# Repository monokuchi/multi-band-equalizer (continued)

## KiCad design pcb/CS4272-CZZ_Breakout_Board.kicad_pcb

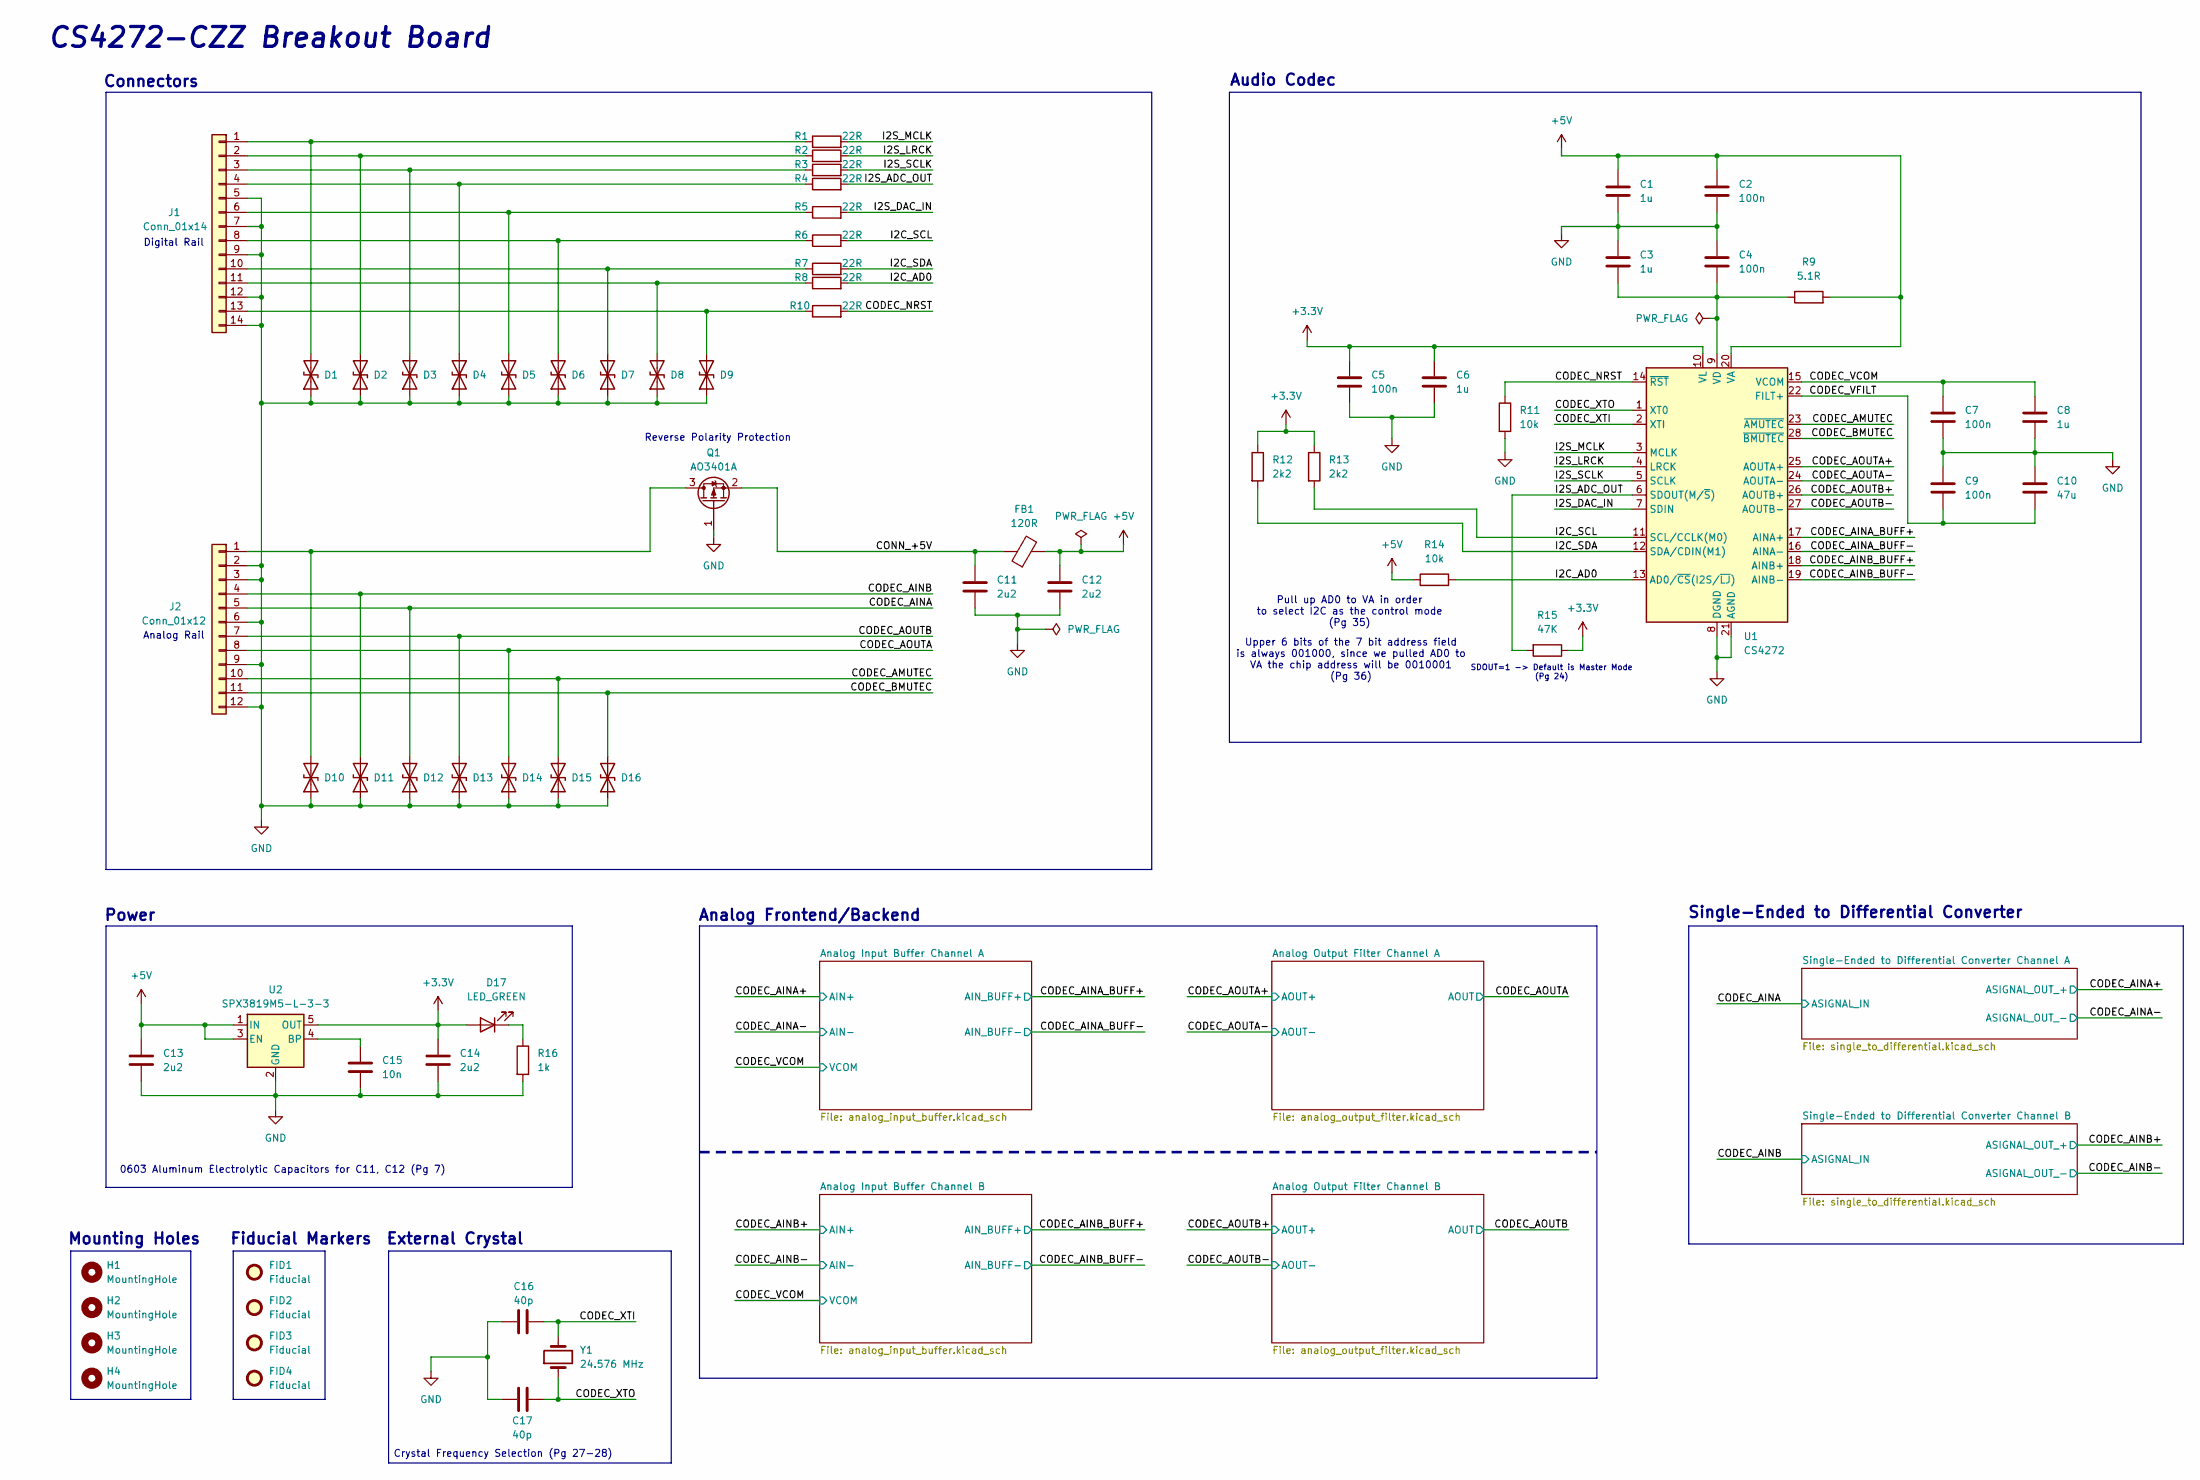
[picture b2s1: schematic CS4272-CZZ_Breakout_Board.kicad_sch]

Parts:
C1, C3, C6, C8: 1u; C_0805_2012Metric
C2, C4, C5, C7, C9: 100n; C_0805_2012Metric
C10: 47u; C_0805_2012Metric
C11, C12, C13, C14: 2u2; C_0805_2012Metric
C15: 10n; C_0805_2012Metric
C16, C17: 40p; C_0805_2012Metric
D1, D2, D3, D4, D5, D6, D7, D8, D9, D10, D11, D12, D13, D14, D15, D16: D_TVS; D_0805_2012Metric
D17: LED_GREEN; LED_0805_2012Metric
FB1: 120R; L_0805_2012Metric
FID1, FID2, FID3, FID4: Fiducial; Fiducial_1mm_Mask3mm
H1, H2, H3, H4: MountingHole; MountingHole_2.2mm_M2
J1: Conn_01x14; PinHeader_1x14_P2.54mm_Vertical
J2: Conn_01x12; PinHeader_1x12_P2.54mm_Vertical
Q1: AO3401A; SOT-23
R1, R2, R3, R4, R5, R6, R7, R8, R10: 22R; R_0805_2012Metric
R9: 5.1R; R_0805_2012Metric
R11, R14: 10k; R_0805_2012Metric
R12, R13: 2k2; R_0805_2012Metric
R15: 47K; R_0805_2012Metric
R16: 1k; R_0805_2012Metric
U1: CS4272; TSSOP-28_4.4x9.7mm_P0.65mm
U2: SPX3819M5-L-3-3; SOT-23-5
Y1: 24.576 MHz; Crystal_HC49-4H_Vertical

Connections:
+3.3V: C5.1, C6.1, C14.1, D17.2 (A), R12.1, R13.1, R15.1, U1.10 (VL), U2.5 (OUT)
+5V: C1.1, C2.1, C12.1, C13.1, FB1.2, R9.2, R14.1, U1.20 (VA), U2.1 (IN), U2.3 (EN); also elsewhere on the board
/CODEC_AINA: D12.2 (A2), J2.5; also elsewhere on the board
/CODEC_AINA_BUFF+: U1.17 (AINA+); also elsewhere on the board
/CODEC_AINA_BUFF-: U1.16 (AINA-); also elsewhere on the board
/CODEC_AINB: D11.2 (A2), J2.4; also elsewhere on the board
/CODEC_AINB_BUFF+: U1.18 (AINB+); also elsewhere on the board
/CODEC_AINB_BUFF-: U1.19 (AINB-); also elsewhere on the board
/CODEC_AMUTEC: D15.2 (A2), J2.10, U1.23 (~AMUTEC)
/CODEC_AOUTA: D14.2 (A2), J2.8; also elsewhere on the board
/CODEC_AOUTA+: U1.25 (AOUTA+); also elsewhere on the board
/CODEC_AOUTA-: U1.24 (AOUTA-); also elsewhere on the board
/CODEC_AOUTB: D13.2 (A2), J2.7; also elsewhere on the board
/CODEC_AOUTB+: U1.26 (AOUTB+); also elsewhere on the board
/CODEC_AOUTB-: U1.27 (AOUTB-); also elsewhere on the board
/CODEC_BMUTEC: D16.2 (A2), J2.11, U1.28 (~BMUTEC)
/CODEC_NRST: R10.2, R11.1, U1.14 (~RST)
/CODEC_VCOM: C7.1, C8.1, U1.15 (VCOM); also elsewhere on the board
/CODEC_VFILT: C9.2, C10.2, U1.22 (FILT+)
/CODEC_XTI: C16.1, U1.2 (XTI), Y1.2
/CODEC_XTO: C17.1, U1.1 (XT0), Y1.1
/CONN_+5V: C11.1, FB1.1, Q1.2 (S)
/I2C_AD0: R8.2, R14.2, U1.13 (AD0/~CS(I2S/~LJ))
/I2C_SCL: R6.2, R13.2, U1.11 (SCL/CCLK(M0))
/I2C_SDA: R7.2, R12.2, U1.12 (SDA/CDIN(M1))
/I2S_ADC_OUT: R4.2, R15.2, U1.6 (SDOUT(M/~S))
/I2S_DAC_IN: R5.2, U1.7 (SDIN)
/I2S_LRCK: R2.2, U1.4 (LRCK)
/I2S_MCLK: R1.2, U1.3 (MCLK)
/I2S_SCLK: R3.2, U1.5 (SCLK)
GND: C1.2, C2.2, C3.1, C4.1, C5.2, C6.2, C7.2, C8.2, C9.1, C10.1, C11.2, C12.2, C13.2, C14.2, C15.2, C16.2, C17.2, D1.1 (A1), D2.1 (A1), D3.1 (A1), D4.1 (A1), D5.1 (A1), D6.1 (A1), D7.1 (A1), D8.1 (A1), D9.1 (A1), D10.1 (A1), D11.1 (A1), D12.1 (A1), D13.1 (A1), D14.1 (A1), D15.1 (A1), D16.1 (A1), J1.5, J1.7, J1.9, J1.12, J1.14, J2.2, J2.3, J2.6, J2.9, J2.12, Q1.1 (G), R11.2, R16.2, U1.8 (DGND), U1.21 (AGND), U2.2 (GND); also elsewhere on the board
unnamed: D1.2 (A2), J1.1, R1.1
unnamed: D2.2 (A2), J1.2, R2.1
unnamed: D3.2 (A2), J1.3, R3.1
unnamed: D4.2 (A2), J1.4, R4.1
unnamed: D5.2 (A2), J1.6, R5.1
unnamed: D6.2 (A2), J1.8, R6.1
unnamed: D7.2 (A2), J1.10, R7.1
unnamed: D8.2 (A2), J1.11, R8.1
unnamed: D9.2 (A2), J1.13, R10.1
unnamed: D10.2 (A2), J2.1, Q1.3 (D)
unnamed: D17.1 (K), R16.1
unnamed: C3.2, C4.2, R9.1, U1.9 (VD)
unnamed: C15.1, U2.4 (BP)

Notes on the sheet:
Power
Crystal Frequency Selection (Pg 27-28)
CS4272-CZZ Breakout Board
Pull up AD0 to VA in order to select I2C as the control mode (Pg 35)
Digital Rail
Connectors
Reverse Polarity Protection
Mounting Holes
Analog Frontend/Backend
Upper 6 bits of the 7 bit address field is always 001000, since we pulled AD0 to VA the chip address will be 0010001 (Pg 36)
SDOUT=1 -> Default is Master Mode (Pg 24)
0603 Aluminum Electrolytic Capacitors for C11, C12 (Pg 7)
Audio Codec
Analog Rail
External Crystal
Fiducial Markers
Single-Ended to Differential Converter

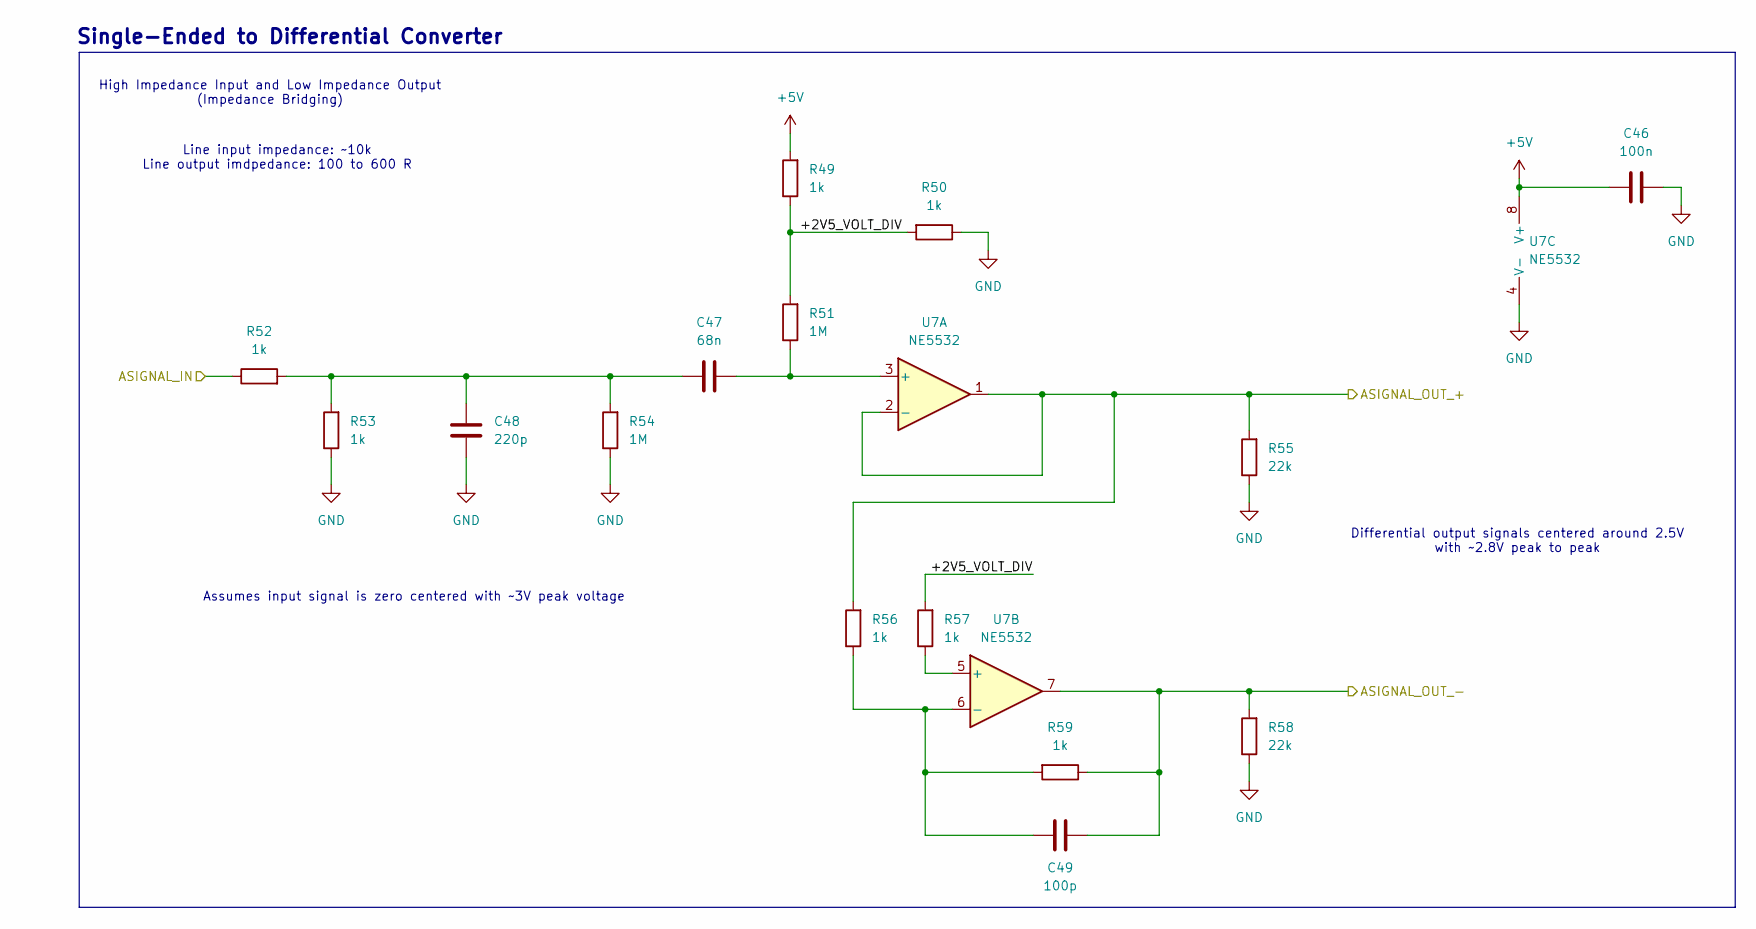
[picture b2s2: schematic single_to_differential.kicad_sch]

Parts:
C46: 100n; C_0805_2012Metric
C47: 68n; C_0805_2012Metric
C48: 220p; C_0805_2012Metric
C49: 100p; C_0805_2012Metric
R49, R50, R52, R53, R56, R57, R59: 1k; R_0805_2012Metric
R51, R54: 1M; R_0805_2012Metric
R55, R58: 22k; R_0805_2012Metric
U7: NE5532; SOIC-8_3.9x4.9mm_P1.27mm

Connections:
+5V: C46.1, R49.2, U7.8 (V+); also elsewhere on the board
/CODEC_AINA: R52.1; also elsewhere on the board
/CODEC_AINA+: R55.2, R56.2, U7.1, U7.2 (-); also elsewhere on the board
/CODEC_AINA-: C49.1, R58.2, R59.1, U7.7; also elsewhere on the board
/Single-Ended to Differential Converter Channel A/+2V5_VOLT_DIV: R49.1, R50.2, R51.2, R57.2
GND: C46.2, C48.2, R50.1, R53.1, R54.1, R55.1, R58.1, U7.4 (V-); also elsewhere on the board
unnamed: C47.1, C48.1, R52.2, R53.2, R54.2
unnamed: C47.2, R51.1, U7.3 (+)
unnamed: R57.1, U7.5 (+)
unnamed: C49.2, R56.1, R59.2, U7.6 (-)

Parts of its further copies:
C50: 100n; C_0805_2012Metric
C51: 68n; C_0805_2012Metric
C52: 220p; C_0805_2012Metric
C53: 100p; C_0805_2012Metric
R60, R61, R63, R64, R67, R68, R70: 1k; R_0805_2012Metric
R62, R65: 1M; R_0805_2012Metric
R66, R69: 22k; R_0805_2012Metric
U8: NE5532; SOIC-8_3.9x4.9mm_P1.27mm

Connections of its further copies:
+5V: C50.1, R60.2, U8.8 (V+); also elsewhere on the board
/CODEC_AINB: R63.1; also elsewhere on the board
/CODEC_AINB+: R66.2, R67.2, U8.1, U8.2 (-); also elsewhere on the board
/CODEC_AINB-: C53.1, R69.2, R70.1, U8.7; also elsewhere on the board
/Single-Ended to Differential Converter Channel B/+2V5_VOLT_DIV: R60.1, R61.2, R62.2, R68.2
GND: C50.2, C52.2, R61.1, R64.1, R65.1, R66.1, R69.1, U8.4 (V-); also elsewhere on the board
unnamed: C51.1, C52.1, R63.2, R64.2, R65.2
unnamed: C51.2, R62.1, U8.3 (+)
unnamed: R68.1, U8.5 (+)
unnamed: C53.2, R67.1, R70.2, U8.6 (-)

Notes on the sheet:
Assumes input signal is zero centered with ~3V peak voltage
Single-Ended to Differential Converter
High Impedance Input and Low Impedance Output (Impedance Bridging)
Differential output signals centered around 2.5V with ~2.8V peak to peak
Line input impedance: ~10k Line output imdpedance: 100 to 600 R

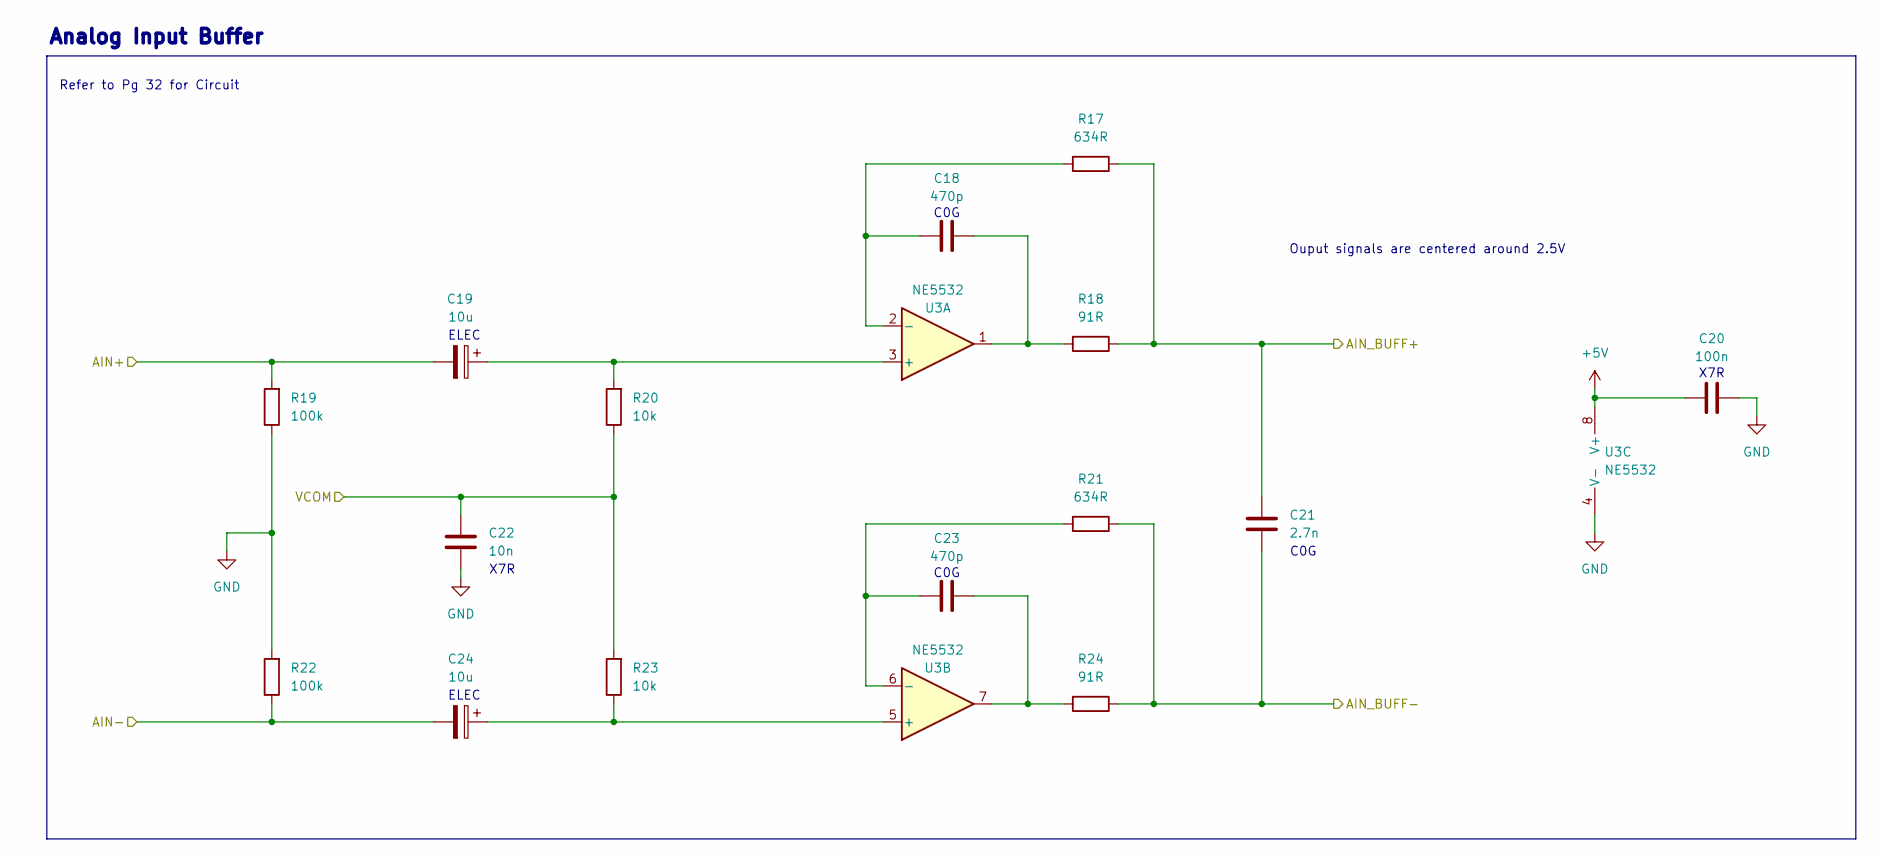
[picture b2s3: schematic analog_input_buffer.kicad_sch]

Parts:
C18, C23: 470p; C_0805_2012Metric
C19, C24: 10u; CP_Elec_5x5.4
C20: 100n; C_0805_2012Metric
C21: 2.7n; C_0805_2012Metric
C22: 10n; C_0805_2012Metric
R17, R21: 634R; R_0805_2012Metric
R18, R24: 91R; R_0805_2012Metric
R19, R22: 100k; R_0805_2012Metric
R20, R23: 10k; R_0805_2012Metric
U3: NE5532; SOIC-8_3.9x4.9mm_P1.27mm

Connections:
+5V: C20.1, U3.8 (V+); also elsewhere on the board
/CODEC_AINA+: C19.2, R19.2; also elsewhere on the board
/CODEC_AINA-: C24.2, R22.1; also elsewhere on the board
/CODEC_AINA_BUFF+: C21.2, R17.1, R18.1; also elsewhere on the board
/CODEC_AINA_BUFF-: C21.1, R21.1, R24.1; also elsewhere on the board
/CODEC_VCOM: C22.1, R20.1, R23.2; also elsewhere on the board
GND: C20.2, C22.2, R19.1, R22.2, U3.4 (V-); also elsewhere on the board
unnamed: C18.2, R18.2, U3.1
unnamed: C23.2, R24.2, U3.7
unnamed: C19.1, R20.2, U3.3 (+)
unnamed: C18.1, R17.2, U3.2 (-)
unnamed: C24.1, R23.1, U3.5 (+)
unnamed: C23.1, R21.2, U3.6 (-)

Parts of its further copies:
C32, C37: 470p; C_0805_2012Metric
C33, C38: 10u; CP_Elec_5x5.4
C34: 100n; C_0805_2012Metric
C35: 2.7n; C_0805_2012Metric
C36: 10n; C_0805_2012Metric
R33, R37: 634R; R_0805_2012Metric
R34, R40: 91R; R_0805_2012Metric
R35, R38: 100k; R_0805_2012Metric
R36, R39: 10k; R_0805_2012Metric
U5: NE5532; SOIC-8_3.9x4.9mm_P1.27mm

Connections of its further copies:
+5V: C34.1, U5.8 (V+); also elsewhere on the board
/CODEC_AINB+: C33.2, R35.2; also elsewhere on the board
/CODEC_AINB-: C38.2, R38.1; also elsewhere on the board
/CODEC_AINB_BUFF+: C35.2, R33.1, R34.1; also elsewhere on the board
/CODEC_AINB_BUFF-: C35.1, R37.1, R40.1; also elsewhere on the board
/CODEC_VCOM: C36.1, R36.1, R39.2; also elsewhere on the board
GND: C34.2, C36.2, R35.1, R38.2, U5.4 (V-); also elsewhere on the board
unnamed: C32.2, R34.2, U5.1
unnamed: C37.2, R40.2, U5.7
unnamed: C33.1, R36.2, U5.3 (+)
unnamed: C32.1, R33.2, U5.2 (-)
unnamed: C38.1, R39.1, U5.5 (+)
unnamed: C37.1, R37.2, U5.6 (-)

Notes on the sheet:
C0G
Analog Input Buffer
X7R
Refer to Pg 32 for Circuit
Ouput signals are centered around 2.5V
ELEC

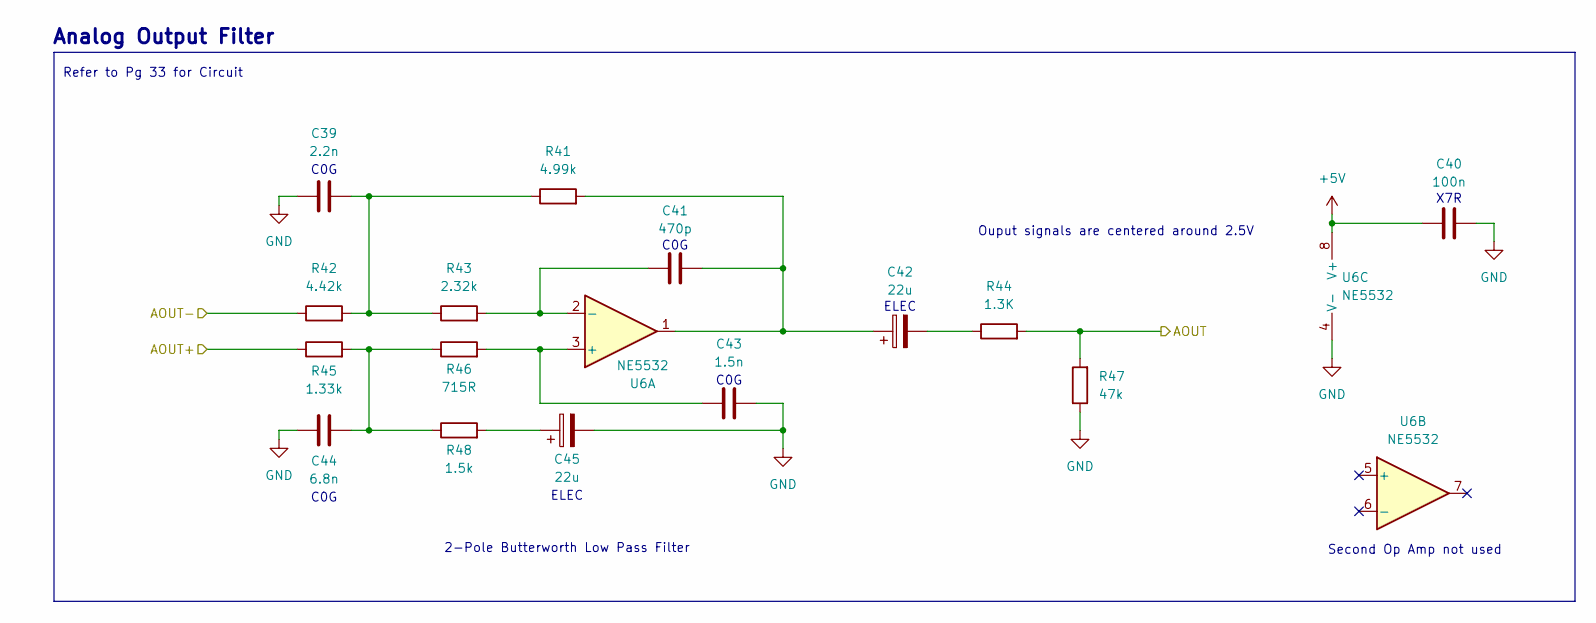
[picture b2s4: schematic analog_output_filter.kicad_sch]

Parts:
C39: 2.2n; C_0805_2012Metric
C40: 100n; C_0805_2012Metric
C41: 470p; C_0805_2012Metric
C42, C45: 22u; CP_Elec_4x5.4
C43: 1.5n; C_0805_2012Metric
C44: 6.8n; C_0805_2012Metric
R41: 4.99k; R_0805_2012Metric
R42: 4.42k; R_0805_2012Metric
R43: 2.32k; R_0805_2012Metric
R44: 1.3K; R_0805_2012Metric
R45: 1.33k; R_0805_2012Metric
R46: 715R; R_0805_2012Metric
R47: 47k; R_0805_2012Metric
R48: 1.5k; R_0805_2012Metric
U6: NE5532; SOIC-8_3.9x4.9mm_P1.27mm

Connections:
+5V: C40.1, U6.8 (V+); also elsewhere on the board
/CODEC_AOUTB: R44.2, R47.2; also elsewhere on the board
/CODEC_AOUTB+: R45.1; also elsewhere on the board
/CODEC_AOUTB-: R42.1; also elsewhere on the board
GND: C39.1, C40.2, C43.2, C44.1, C45.2, R47.1, U6.4 (V-); also elsewhere on the board
unnamed: C39.2, R41.1, R42.2, R43.1
unnamed: C41.2, C42.1, R41.2, U6.1
unnamed: C42.2, R44.1
unnamed: C44.2, R45.2, R46.1, R48.1
unnamed: C45.1, R48.2
unnamed: C43.1, R46.2, U6.3 (+)
unnamed: C41.1, R43.2, U6.2 (-)

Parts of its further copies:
C25: 2.2n; C_0805_2012Metric
C26: 100n; C_0805_2012Metric
C27: 470p; C_0805_2012Metric
C28, C31: 22u; CP_Elec_4x5.4
C29: 1.5n; C_0805_2012Metric
C30: 6.8n; C_0805_2012Metric
R25: 4.99k; R_0805_2012Metric
R26: 4.42k; R_0805_2012Metric
R27: 2.32k; R_0805_2012Metric
R28: 1.3K; R_0805_2012Metric
R29: 1.33k; R_0805_2012Metric
R30: 715R; R_0805_2012Metric
R31: 47k; R_0805_2012Metric
R32: 1.5k; R_0805_2012Metric
U4: NE5532; SOIC-8_3.9x4.9mm_P1.27mm

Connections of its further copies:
+5V: C26.1, U4.8 (V+); also elsewhere on the board
/CODEC_AOUTA: R28.2, R31.2; also elsewhere on the board
/CODEC_AOUTA+: R29.1; also elsewhere on the board
/CODEC_AOUTA-: R26.1; also elsewhere on the board
GND: C25.1, C26.2, C29.2, C30.1, C31.2, R31.1, U4.4 (V-); also elsewhere on the board
unnamed: C25.2, R25.1, R26.2, R27.1
unnamed: C27.2, C28.1, R25.2, U4.1
unnamed: C28.2, R28.1
unnamed: C30.2, R29.2, R30.1, R32.1
unnamed: C31.1, R32.2
unnamed: C29.1, R30.2, U4.3 (+)
unnamed: C27.1, R27.2, U4.2 (-)

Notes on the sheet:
C0G
Refer to Pg 33 for Circuit
X7R
2-Pole Butterworth Low Pass Filter
Second Op Amp not used
Ouput signals are centered around 2.5V
ELEC
Analog Output Filter

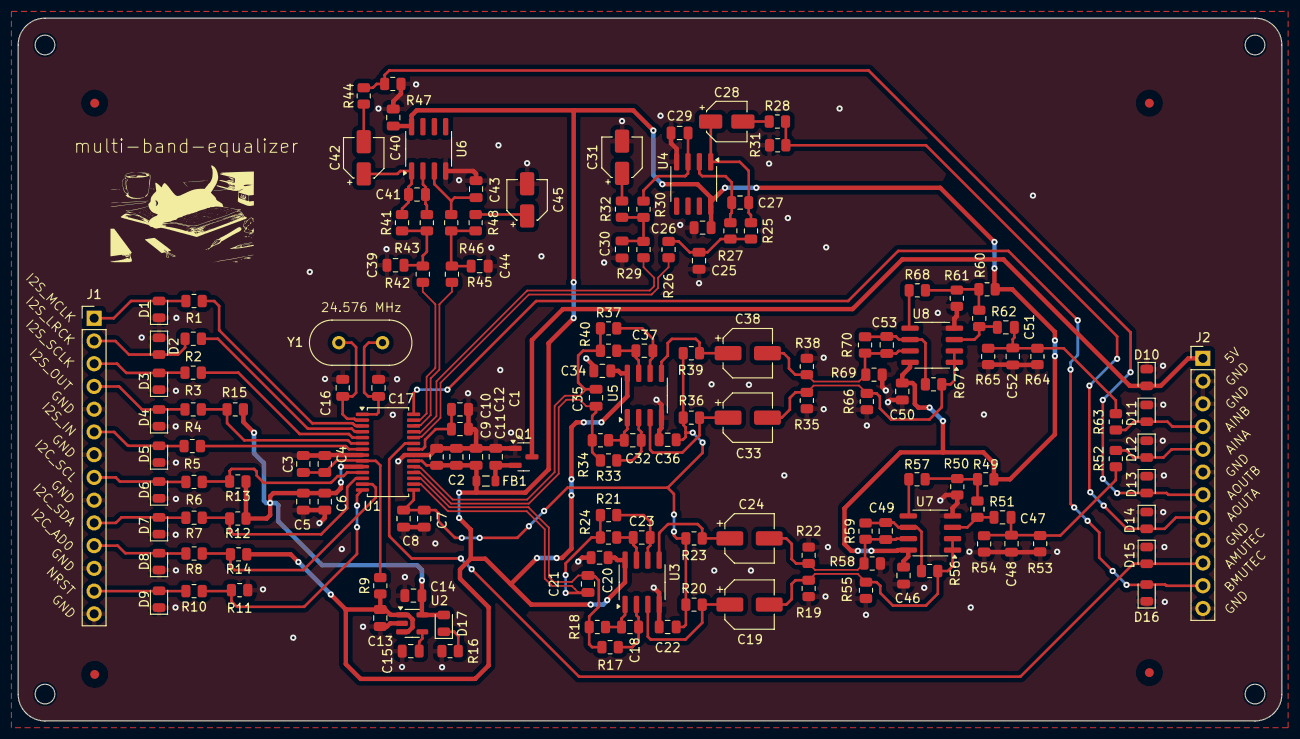
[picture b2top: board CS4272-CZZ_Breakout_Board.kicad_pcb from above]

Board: 2 copper layers, 141.1 x 78.5 mm, 161 parts (0 on the bottom side), 84 nets.

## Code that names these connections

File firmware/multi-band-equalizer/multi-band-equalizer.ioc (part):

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Mcu.Name=STM32H7B0VBTx
Mcu.Package=LQFP100
Mcu.UserName=STM32H7B0VBTx
PA1.GPIOParameters=GPIO_Label
PA1.GPIO_Label=CTRL_KNB_VOL_LVL
PA1.Mode=IN17-Single-Ended
PA1.Signal=ADC1_INP17
PA13.Mode=Trace_Asynchronous_SW
PA13.Signal=DEBUG_JTMS-SWDIO
PA14.Mode=Trace_Asynchronous_SW
PA14.Signal=DEBUG_JTCK-SWCLK
PA2.GPIOParameters=GPIO_Label
PA2.GPIO_Label=CTRL_KNB_12800_HZ
PA2.Signal=ADCx_INP14
PA3.GPIOParameters=GPIO_Label
PA3.GPIO_Label=CTRL_KNB_6400_HZ
PA3.Mode=IN15-Single-Ended
PA3.Signal=ADC1_INP15
PA4.GPIOParameters=GPIO_Label
PA4.GPIO_Label=CTRL_KNB_3200_HZ
PA4.Signal=ADCx_INP18
PA5.GPIOParameters=GPIO_Label
PA5.GPIO_Label=CTRL_KNB_1600_HZ
PA5.Signal=ADCx_INP19
PA6.GPIOParameters=GPIO_Label
PA6.GPIO_Label=CTRL_KNB_800_HZ
PA6.Signal=ADCx_INP3
PA7.GPIOParameters=GPIO_Label
PA7.GPIO_Label=CTRL_KNB_400_HZ
PA7.Signal=ADCx_INP7
PB0.GPIOParameters=GPIO_Label
PB0.GPIO_Label=CTRL_KNB_60_HZ
PB0.Signal=ADCx_INP9
PB1.GPIOParameters=GPIO_Label
PB1.GPIO_Label=CTRL_KNB_30_HZ
PB1.Signal=ADCx_INP5
PB10.Mode=I2C
PB10.Signal=I2C2_SCL
PB11.Mode=I2C
PB11.Signal=I2C2_SDA
PB12.GPIOParameters=GPIO_Label
PB12.GPIO_Label=I2S2_LRCK
PB12.Mode=Full_Duplex_Master
PB12.Signal=I2S2_WS
PB13.GPIOParameters=GPIO_Label
PB13.GPIO_Label=I2S2_SCLK
PB13.Mode=Full_Duplex_Master
PB13.Signal=I2S2_CK
PB14.Mode=Full_Duplex_Master
PB14.Signal=I2S2_SDI
PB15.Mode=Full_Duplex_Master
PB15.Signal=I2S2_SDO
PB3.Mode=Trace_Asynchronous_SW
PB3.Signal=DEBUG_JTDO-SWO
PC4.GPIOParameters=GPIO_Label
PC4.GPIO_Label=CTRL_KNB_200_HZ
PC4.Signal=ADCx_INP4
PC5.GPIOParameters=GPIO_Label
PC5.GPIO_Label=CTRL_KNB_120_HZ
PC5.Signal=ADCx_INP8
PC6.GPIOParameters=GPIO_Label
PC6.GPIO_Label=I2S2_MCLK
PC6.Mode=Master_Clock_Activated
PC6.Signal=I2S2_MCK
PE12.GPIOParameters=GPIO_Label
PE12.GPIO_Label=LED_STATUS_RED
PE12.Signal=GPIO_Output
PE8.GPIOParameters=GPIO_Label
PE8.GPIO_Label=CODEC_NRST
PE8.Signal=GPIO_Output
PH0-OSC_IN.Mode=HSE-External-Oscillator
PH0-OSC_IN.Signal=RCC_OSC_IN
PH1-OSC_OUT.Mode=HSE-External-Oscillator
PH1-OSC_OUT.Signal=RCC_OSC_OUT
RCC.SYSCLKFreq_VALUE=270000000
RCC.SYSCLKSource=RCC_SYSCLKSOURCE_PLLCLK
board=custom

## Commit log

2024-08-09 PCB update
2024-08-19 Update Ver 1
2024-08-22 organization
2024-08-22 update gitignore
2024-08-25 firmware
2024-08-26 firmware update
2024-09-15 Fixed register values
2024-09-21 Fixed DSP
2024-09-21 Added multi-band-equalizer PCB
2024-09-22 Fixed peaking filter calculation
2024-09-23 Renamed firmware project
2024-09-27 pcb updates
2024-10-05 Fix i2s and filter calculations
2024-10-13 Added CMSIS
2024-10-14 Update schematic
2024-10-18 Fixed CMSIS implementation
2024-10-18 Inital firmware for v2
2024-10-20 sliding potentiometers
2024-10-24 Added custom pcb libraries
2024-10-25 Update pcb
2024-10-27 Updated pcb and script
2024-10-27 remove simulation data
2024-10-27 update firmwares
2024-10-28 fixed plotting script
2024-10-28 Clean up code
2024-11-03 update submodule
2024-11-09 stitching vias
2024-11-09 update firmware
2024-11-15 new gerbers
2024-11-16 resistor value
2024-11-28 add chassis drawing
